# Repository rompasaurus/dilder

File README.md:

# Dilder

A Tamagotchi-inspired virtual pet built on a Raspberry Pi Pico W with an e-ink display, battery pack, and 3D-printed case — developed entirely in the open as a learning platform, blog series, and YouTube companion project.

The goal isn't just to build a thing — it's to show *how* the thing gets built, from the very first idea to a finished handheld device. Every prompt, every design decision, every dead end is documented so anyone can follow along, learn, and build their own.

---

## How It Started — Meet Jamal

<p align="center">
  
  <br />
  <em>Jamal. The plush octopus who started it all.</em>
</p>

This project didn't start with a schematic or a product spec. It started in a TEDi — a German dollar store — where my wife Emma and I found a giant plush octopus grinning up from a discount bin. We bought him on the spot, and on the walk home we started giving him a personality: laid-back, opinionated, a little sassy, suspiciously wise for a boneless creature. By the time we got home, he had a name — **Jamal** — and he'd claimed the armchair like he'd been paying rent.

The question asked itself: *what if we could actually bring him to life?* Not literally — but as a tiny digital companion. A pocket-sized octopus with moods, opinions, and an attitude problem, living on an e-ink screen and judging your life choices in ALL CAPS.

That's how Dilder was born. Not from an engineering roadmap, but from a stuffed animal and two people who couldn't stop anthropomorphizing it on a walk home.

---

## Enclosure — Rev 2 Mk2

The 3D-printed enclosure is a three-part design: base plate with solar panel recess, AAA battery cradle insert, and top cover with display window and joystick cutout. Designed in OpenSCAD (parametric source) and FreeCAD (visual PartDesign).

### Individual Parts

<p align="center">
  <em>Left: Base plate with cradle pocket, corner pillars, battery rail troughs, and USB-C cutout. Right: AAA battery cradle with dual bays, clip slots, and TP4056 indent.</em>
</p>

<p align="center">
  <em>Left: Top cover with display window, joystick hole, and bullnose edge. Right: Base plate bottom showing solar panel recess and wire holes.</em>
</p>

### Assembled

<p align="center">
  
  <br />
  <em>All three parts stacked in their mated positions.</em>
</p>

### Full Assembly with Electronics

The FreeCAD macro now imports the official Raspberry Pi Pico 2 STEP file (mechanically identical to the Pico 2 W) and adds procedural 2×20 pin headers. It also builds three more peripherals from datasheet dimensions — two AAA Li-Ion cells in the cradle bays, a TP4056 USB-C charge module in the connecting block indent, and a Waveshare 2.13" e-paper display in the top cover's screen inlay. The Pico is mounted upside-down with its component-side face flush against the cradle's mating plane, headers extending up into the PicoNest cavity.

<p align="center">
  
  <br />
  <em>Top cover rendered translucent so the Pico 2 W board, headers, and cradle are all visible.</em>
</p>

<p align="center">
  <em>Left: top cover hidden so the cradle and Pico are exposed. Right: cradle hidden so the Pico's seating on the base plate is visible — header pin tips reach the level where the cradle would clip in.</em>
</p>

See the [FreeCAD macro reference](website/docs/docs/hardware/freecad-mk2-macro.md) for a full walkthrough of how the macro is structured.

### Joystick Thumbpiece

A printable snap cap that fits over the K1-1506SN-01 5-way switch peg. Single disc, 11 mm OD (= cover hole − 1 mm) so it nests inside the cover's joystick cutout with 0.5 mm radial clearance for directional swing. Concave thumb dish on top, rectangular snap socket on the bottom centered on the actuator (the SW1 stick is offset +0.68 mm in Y from the cover hole on the production PCB layout — disc reads visually centered, socket lands on the peg). Built parametrically in `dilder_rev2_mk2.FCMacro` as a separate `Thumbpiece` Body — drop `thumb_sock_x/y` from 3.3 to ~3.15 in the spreadsheet to convert friction-fit to interference snap-fit.

<p align="center">
  
  <br />
  <em>Top-down view of the assembled prototype — display window on the left, joystick with the new thumbpiece on the right.</em>
</p>

<p align="center">
  <em>Left: joystick area in context. Right: thumbpiece nested in the cover cutout with the cover dialed to 85% transparency for clarity.</em>
</p>

See the [thumbpiece design write-up](website/docs/blog/posts/joystick-thumbpiece-snap-cap.md) for the geometry walkthrough — including the dish-vs-socket constraint that almost ruined the first cut.

---

## What This Project Is

- **A virtual pet device** — a pocket-sized, low-power companion with personality, needs, and interactions displayed on an e-ink screen
- **A build series** — a step-by-step guide covering hardware, software, 3D printing, and project planning
- **A transparency experiment** — the entire development process is captured in real time, including AI-assisted prompts, iteration, and mistakes

---

## Hardware

### Phase 1 — Pico 2 W Prototype (current)

| Component | Details |
|-----------|---------|
| Board | Raspberry Pi Pico 2 W (RP2350, 40-pin headers) |
| Display | [Waveshare Pico-ePaper-2.13](https://www.waveshare.com/pico-epaper-2.13.htm) — 250x122px, black & white, SPI1, SSD1680 driver |
| Power | TP4056 USB-C charger module + LiPo 1000mAh (3.7V on VSYS) |
| Input | DollaTek K1-1506SN-01 5-way joystick (GP2-GP6) |
| Sound | Active buzzer on GP14 (3-12V, GPIO on/off) |
| Motion | MPU-6050 accelerometer/gyroscope on I2C0 (GP0/GP1, 400kHz) |

### Future — Pi Zero Upgrade

| Component | Details |
|-----------|---------|
| Board | Raspberry Pi Zero WH (W or 2 W, pre-soldered headers) |
| Power | LiPo battery + Adafruit PowerBoost 500C |
| Enclosure | 3D-printed case (STL files provided) |

> The Pico W is the starting platform — it's what we have on hand, it's cheap, and it's excellent for prototyping the display and input system. The Pi Zero upgrade comes later when we need Linux, networking features, or more compute.

---

## Phases

Each phase maps to a section of the blog/YouTube series and can be followed independently.

### Phase 0 — Project Planning & Documentation ✓

- [x] Create repository and project structure
- [x] Define project intent and scope
- [x] Begin prompt progression log ([PromptProgression.md](PromptProgression.md))
- [x] Outline full phase roadmap
- [x] Create pixel art concepts for e-ink display (octopus character with 16 emotional states)
- [x] Define enclosure concept and prototype dimensions

### Phase 1 — Hardware Selection & Setup (Pico W) ✓

- [x] Finalize component list with links/part numbers ([hardware-research.md](docs/hardware-research.md))
- [x] Set up Docker-based C SDK cross-compilation toolchain
- [x] Wire e-ink display to Pico W via jumper wires (SPI)
- [x] Flash and run "Hello, Dilder!" on the e-ink display — proof of life
- [x] Build DevTool GUI — display emulator, serial monitor, firmware flash, asset manager, GPIO reference, connection utility, documentation ([tools/devtool/](tools/devtool/))
- [x] Add Programs tab with animated octopus preview, firmware size estimation, and deploy
- [x] Build IMG-receiver firmware — stream images from PC to Pico display via USB serial ([dev-setup/img-receiver/](dev-setup/img-receiver/))
- [x] Build standalone deploy — runtime-rendered animation, runs without PC
- [x] Wire and test joystick input (DollaTek 5-way, GP2-GP6)
- [x] Battery power prototype (TP4056 USB-C + LiPo on VSYS, ADC3 voltage sense)

### Phase 2 — Firmware Foundation (C on Pico W)
> *You are here*

- [x] Runtime rendering engine — draw octopus mathematically (no pre-baked frames)
- [x] Animation system — 4-frame mouth cycle with per-mood expression sequences
- [x] Body transform system — dx/dy offset, x_expand, per-row sine wobble
- [x] Custom body shapes for Fat (wider dome, thick tentacles) and Lazy (tentacles draped right)
- [x] 16 emotional states with unique eyes, pupils, eyebrows, eyelids, mouths, and body animations
- [x] 17 standalone firmware programs (16 emotions + mood selector with all 823 quotes)
- [x] Date/time clock header from RTC
- [x] C-faithful preview renderer for verifying firmware matches DevTool
- [x] Keyboard-to-Pico input mapping plan ([docs/keyboard-to-pico-input.md](docs/keyboard-to-pico-input.md))
- [x] Implement serial command input for interactive mood control
- [x] Wire and test GPIO joystick input (DollaTek 5-way, GP2–GP6)
- [x] Joystick Mood Selector firmware with on-screen input indicator
- [ ] **Custom PCB design (in progress)** — switched MCU from RP2040 to ESP32-S3-WROOM-1-N16R8 (WiFi+BLE, 16MB flash, 8MB PSRAM). 4-layer board (45x80mm, 30 components) in KiCad, ready for routing. Target fab: JLCPCB. Sensors: LIS2DH12TR (accelerometer), AHT20 (temperature/humidity), BH1750FVI-TR (ambient light) on shared I2C bus.
- [ ] Battery power (LiPo on VSYS) — InnCraft 1000mAh acquired
- [ ] Build game loop with state machine (idle, interact, sleep)

### Phase 3 — Pet Logic & Gameplay

- [ ] Define pet stats (hunger, happiness, energy, health, etc.)
- [ ] Implement stat decay over time
- [ ] Build interaction system — feed, play, sleep, clean
- [x] Pet mood / expressions based on emotional states (16 implemented)
- [x] Animation frames for e-ink (idle expressions, body movement per mood)
- [ ] Emotional state transitions triggered by interactions and stats
- [ ] Add death/game-over state and reset/new-pet flow

### Phase 4 — UI & Menus
> *Major progress*

- [x] Menu system with scrolling navigation (joystick up/down/center/left-back)
- [x] Status bar — WiFi icon (top-left), battery icon with percentage (top-right), RTC clock header
- [x] Screen transitions between octopus, menu overlay, and sub-screens (10 states)
- [x] Sound settings — on/off, volume (low/med/high), 6 test patterns
- [x] WiFi submenu — on/off toggle, network scanning, on-screen keyboard for password entry
- [x] Motion menu — live accelerometer/gyro, pedometer, tilt, threshold adjust, I2C scanner
- [x] Device info — firmware version, build date, battery voltage, WiFi status, NTP sync
- [ ] Implement settings screen (name pet, reset)

### Phase 5 — Pi Zero Migration

- [ ] Port MicroPython firmware to CPython on Pi Zero
- [ ] Set up headless Raspberry Pi OS
- [ ] Adapt display driver for Pi Zero SPI + Waveshare HAT
- [ ] Adapt input handler for Pi Zero GPIO
- [ ] Validate all Phase 2-4 functionality on Pi Zero

### Phase 6 — 3D-Printed Case & Power
> *In progress alongside Phase 2*

- [x] Design enclosure in OpenSCAD — parametric 3-part design (base plate, AAA cradle, top cover)
- [x] Account for display cutout, joystick access, USB-C charging port, solar panel recess
- [x] Translate to FreeCAD PartDesign — full parametric model with 90+ parameter spreadsheet
- [x] Battery cradle with clip slots for Swpeet AAA contact plates (parallel wiring)
- [x] Solar panel wire through-holes in base plate
- [x] Print prototypes and iterate on fit (Rev 2 Mk2 current)
- [x] Implement battery power (LiPo 1000mAh via TP4056 USB-C on VSYS)
- [ ] Implement sleep/wake cycle to conserve battery (see [power report](hardware-design/power-consumption-report.md))
- [x] Publish STL/3MF files and build instructions ([hardware-design/freecad-mk2/](hardware-design/freecad-mk2/))

### Phase 7 — Extras & Community

- [x] Add sound — active buzzer with 6 patterns (beep, chirp, SOS, doorbell, alert, happy)
- [x] WiFi connectivity — network scanning, on-screen keyboard, connect to any network
- [x] MPU-6050 accelerometer/gyroscope with pedometer and tilt sensing
- [ ] Explore connectivity — Bluetooth pet interactions?
- [ ] Mini-games
- [ ] Seasonal/event-based pet outfits or moods
- [ ] Publish a "build your own" kit guide
- [ ] Community gallery — show off your Dilder

---

## Content & Documentation

| Resource | Description |
|----------|-------------|
| [PromptProgression.md](PromptProgression.md) | Every AI prompt used in development (104+), timestamped with token counts and file changes |
| [docs/hardware-research.md](docs/hardware-research.md) | Component research, materials list, GPIO pinout, and enclosure concepts |
| [docs/mpu6050-wiring-guide.md](docs/mpu6050-wiring-guide.md) | MPU-6050 accelerometer wiring, I2C details, and register reference |
| [hardware-design/power-consumption-report.md](hardware-design/power-consumption-report.md) | Full power budget, battery life projections, and reduction strategies |
| [docs/session-2026-05-07-implementation.md](docs/session-2026-05-07-implementation.md) | May 7 session — WiFi scan, keyboard, sound, MPU-6050, active buzzer |
| [Emotion States](https://dilder.dev/docs/software/emotion-states/) | All 16 emotional states with rendered previews and animation strips |
| [docs/keyboard-to-pico-input.md](docs/keyboard-to-pico-input.md) | Input mapping plan for interactive octopus control |
| [Blog](https://dilder.dev/blog/) | Build journal — 8 posts covering planning through body animations |
| YouTube (TBD) | Video walkthroughs for each phase |

---

## Follow Along

This project is built in the open. Star/watch this repo to follow progress. Each phase will have a corresponding blog post and video.

---

## License

TBD

---

*Built with patience, a Pico W, and an unreasonable fondness for a plush octopus named Jamal.*

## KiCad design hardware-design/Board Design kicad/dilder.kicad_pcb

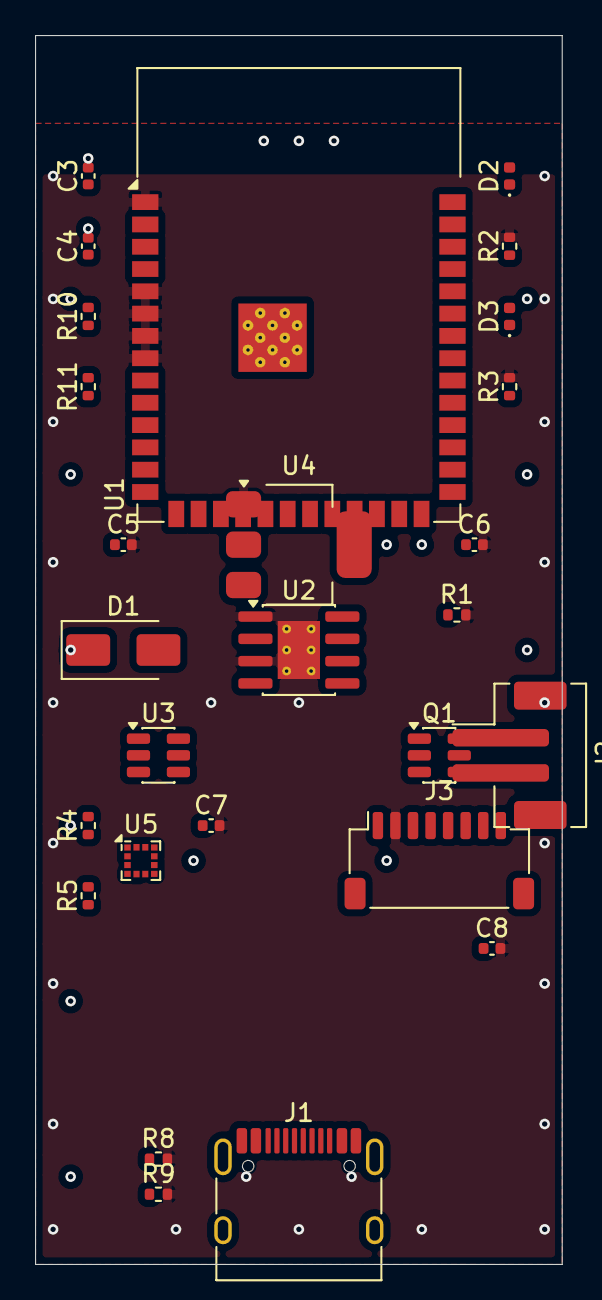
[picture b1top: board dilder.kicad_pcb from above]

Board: 4 copper layers, 30.0 x 70.0 mm, 27 parts (0 on the bottom side), 23 nets, no tracks yet.

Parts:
C3, C7, C8: 100nF; C_0402_1005Metric
C4, C5, C6: 10uF; C_0402_1005Metric
D1: SS34; D_SMA
D2: RED; LED_0402_1005Metric
D3: GREEN; LED_0402_1005Metric
J1: USB-C; USB_C_Receptacle_HRO_TYPE-C-31-M-12
J2: BAT; JST_PH_B2B-PH-SM4-TB_1x02-1MP_P2.00mm_Vertical
J3: ePaper; JST_SH_SM08B-SRSS-TB_1x08-1MP_P1.00mm_Horizontal
Q1: FS8205A; SOT-23-6
R1: 1.2k; R_0402_1005Metric
R2, R3: 1k; R_0402_1005Metric
R4, R5, R10, R11: 10k; R_0402_1005Metric
R8, R9: 5.1k; R_0402_1005Metric
U1: ESP32-S3-WROOM-1-N16R8; ESP32-S3-WROOM-1
U2: TP4056; SOIC-8-1EP_3.9x4.9mm_P1.27mm_EP2.41x3.3mm_ThermalVias
U3: DW01A; SOT-23-6
U4: AMS1117-3.3; SOT-223-3_TabPin2
U5: LIS2DH12TR; LGA-12_2x2mm_P0.5mm

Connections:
3V3: C3.1, C4.1, C6.1, C7.1, J3.1, R4.1, R5.1, R10.1, R11.1, U1.2, U4.2, U5.2, U5.9
/ACCEL_INT1: U1.11, U5.12
/BAT_MINUS: J2.2, Q1.1
/BOOT: R11.2, U1.27
/CC1: J1.A5, R8.1
/CC2: J1.B5, R9.1
/CS_DRAIN: Q1.3, Q1.4, U3.2, U3.6
/EN: C8.1, R10.2, U1.3
/EPD_BUSY: J3.8, U1.20
/EPD_CLK: J3.4, U1.15
/EPD_CS: J3.5, U1.19
/EPD_DC: J3.6, U1.17
/EPD_MOSI: J3.3, U1.16
/EPD_RST: J3.7, U1.18
/I2C_SCL: R5.2, U1.10, U5.1
/I2C_SDA: R4.2, U1.9, U5.4
/OC: Q1.5, U3.3
/OD: Q1.2, U3.1
/USB_DM: J1.A7, U1.13
/USB_DP: J1.A6, U1.14
/VBAT: C5.1, J2.1, U2.5, U3.4, U3.5, U4.3
/VBUS_CHG: U2.4, U2.8
GND: C3.2, C4.2, C5.2, C6.2, C7.2, C8.2, J1.A1, J3.2, Q1.6, R1.2, R2.2, R3.2, R8.2, R9.2, U1.1, U1.5, U1.6, U1.7, U1.8, U2.1, U2.3, U2.9, U4.1, U5.3, U5.6

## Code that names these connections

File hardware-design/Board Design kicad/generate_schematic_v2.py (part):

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        "EN": "EN", "GPIO0": "BOOT",
        "GPIO4": "JOY_UP", "GPIO5": "JOY_DOWN", "GPIO6": "JOY_LEFT",
        "GPIO7": "JOY_RIGHT", "GPIO8": "JOY_CENTER",
        "GPIO16": "I2C_SDA", "GPIO17": "I2C_SCL", "GPIO18": "ACCEL_INT1",
        "GPIO19": "USB_DM", "GPIO20": "USB_DP",
    }
    for pname, lx, ly in left_pins:
        p = pp(U1x, U1y, lx, ly)
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
    # ESP32 right-side labels (SPI ePaper)
    right_pins = [
        ("GPIO9",  17.78, 17.78, "EPD_CLK"),
        ("GPIO10", 17.78, 15.24, "EPD_MOSI"),
        ("GPIO3",  17.78, 12.7,  "EPD_DC"),
        ("GPIO11", 17.78, 10.16, "EPD_RST"),
        ("GPIO46", 17.78, 7.62,  "EPD_CS"),
        ("GPIO12", 17.78, 5.08,  "EPD_BUSY"),
    ]
    for pname, rx, ry, net in right_pins:
        p = pp(U1x, U1y, rx, ry)
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
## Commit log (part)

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2026-04-09 updated project name to more fitting dilder
2026-04-09 Deployed 95e40ed with MkDocs version: 1.6.1
2026-04-09 dd CNAME for custom domain
2026-04-09 Deployed 9a98733 with MkDocs version: 1.6.1
2026-04-09 Deployed 1c7f210 with MkDocs version: 1.6.1
2026-04-11 Deployed 11fce3a with MkDocs version: 1.6.1
2026-04-11 Deployed 62f2917 with MkDocs version: 1.6.1
2026-04-11 Deployed 8401317 with MkDocs version: 1.6.1
2026-04-12 Deployed 63e696b with MkDocs version: 1.6.1
2026-04-12 Deployed 1e27cb4 with MkDocs version: 1.6.1
2026-04-12 Deployed d61b2ff with MkDocs version: 1.6.1
2026-04-12 Deployed b537fff with MkDocs version: 1.6.1
2026-04-12 Deployed 66e18a0 with MkDocs version: 1.6.1
2026-04-12 Deployed 038ba93 with MkDocs version: 1.6.1
2026-04-12 Deployed b8bdf54 with MkDocs version: 1.6.1
2026-04-12 Deployed d053296 with MkDocs version: 1.6.1
2026-04-12 Deployed 9fc8d8d with MkDocs version: 1.6.1
2026-04-12 Deployed 36b00c9 with MkDocs version: 1.6.1
2026-04-12 Deployed 4e891f6 with MkDocs version: 1.6.1
2026-04-12 Deployed d6559c7 with MkDocs version: 1.6.1
2026-04-12 Deployed 1264cd7 with MkDocs version: 1.6.1
2026-04-13 Deployed 2147300 with MkDocs version: 1.6.1
2026-04-13 Deployed 9379cb0 with MkDocs version: 1.6.1
2026-04-14 Deployed 3e7c6dc with MkDocs version: 1.6.1
2026-04-14 Deployed edb669d with MkDocs version: 1.6.1
2026-04-14 Deployed 98bbf74 with MkDocs version: 1.6.1
2026-04-14 Deployed 83d517c with MkDocs version: 1.6.1
2026-04-14 Deployed a732178 with MkDocs version: 1.6.1
2026-04-15 Deployed 3f46a7b with MkDocs version: 1.6.1
2026-04-15 Deployed 1a1de2a with MkDocs version: 1.6.1
2026-04-15 Deployed d36a617 with MkDocs version: 1.6.1
2026-04-15 Deployed a978ad7 with MkDocs version: 1.6.1
2026-04-17 purged uneedede notes and research
2026-04-18 latest updates
2026-05-07 Deployed 36b478e with MkDocs version: 1.6.1
2026-05-07 macroed freecad save
2026-05-07 Deployed 8c83139 with MkDocs version: 1.6.1
2026-05-08 Deployed 9465317 with MkDocs version: 1.6.1
2026-05-08 Deployed 84da287 with MkDocs version: 1.6.1
2026-05-09 copied in a few component schematics to the full board
2026-05-10 Continued kicad specs
2026-05-16 Deployed 807877e with MkDocs version: 1.6.1
2026-05-16 Deployed 9af1a3c with MkDocs version: 1.6.1
2026-06-06 added a bit of documnetiation
2026-06-06 Firmware: full BLE pairing, status icons + website firmware milestone
    Firmware (dilder-hub):
    - Implement real Bluetooth LE peripheral (BTstack): advertise as
    "Dilder Hub", passkey-secured pairing (DISPLAY_ONLY + MITM), bonding.
    - Custom GATT service (0xFFE0): status characteristic (read/notify,
    "MOOD STEPS") + command characteristic (phone-written byte → fresh quote).
    - Add bt.c/bt.h, dilder.gatt, btstack_config.h; wire BT into the
2026-06-06 Deployed cb57f44 with MkDocs version: 1.6.1
2026-06-06 Firmware: Bluetooth on/off toggle + pocket/idle screen-freeze power saving
    - Bluetooth: add runtime bt_enabled (off by default). CENTER on the
    Bluetooth screen toggles the radio — enable (advertise/pair) or disable
    (dilder_bt_stop → HCI power off) to save power. Screen + footer reflect
    ON / OFF (DISABLED); cyw43 polled only while the radio is active.
    - Power saving: freeze e-ink redraws when not being viewed. Accelerometer
    heuristic (viewing_update / screen_is_viewed / wake_screen, g_screen_idle)
2026-06-06 Deployed 118f989 with MkDocs version: 1.6.1
2026-06-09 pushin some hub updates
2026-06-09 Deployed da93836 with MkDocs version: 1.6.1
2026-06-09 Deployed fb2316c with MkDocs version: 1.6.1
